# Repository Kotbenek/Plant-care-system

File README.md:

# Moved to Codeberg

This repository was moved to Codeberg:
https://codeberg.org/Kotbenek/Plant-care-system

# Plant care system
PCB of the Plant care system

## Board overview

- ATmega32 AVR microcontroller as the heart of the Plant care system
- Terminal block connector for external pump
- Galvanically isolated terminal block connector for external lamp
- AVR ISP connector for AVR programming
- 5V DC input with battery backup:
  - 18650 battery holder for battery operation
  - TP4056 board for battery charging
  - Additional circuitry enabling simultaneous battery charging and system operation
- Microswitch buttons for system parameters setup
- 4-digit 7-segment display for system parameters
- LEDs indicating the currently displayed parameter on 7-segment display

## Images

## External 3D models used in the PCB render

- [TP4056 module](https://grabcad.com/library/03962a-hw107-lithium-battery-charging-module-1)
- [18650 battery holder](https://grabcad.com/library/18650-single-slot-battery-holder-leaded-1)
- [Terminal block](https://grabcad.com/library/degson-dg301-series-5-0mm-terminal-block-pack-1)

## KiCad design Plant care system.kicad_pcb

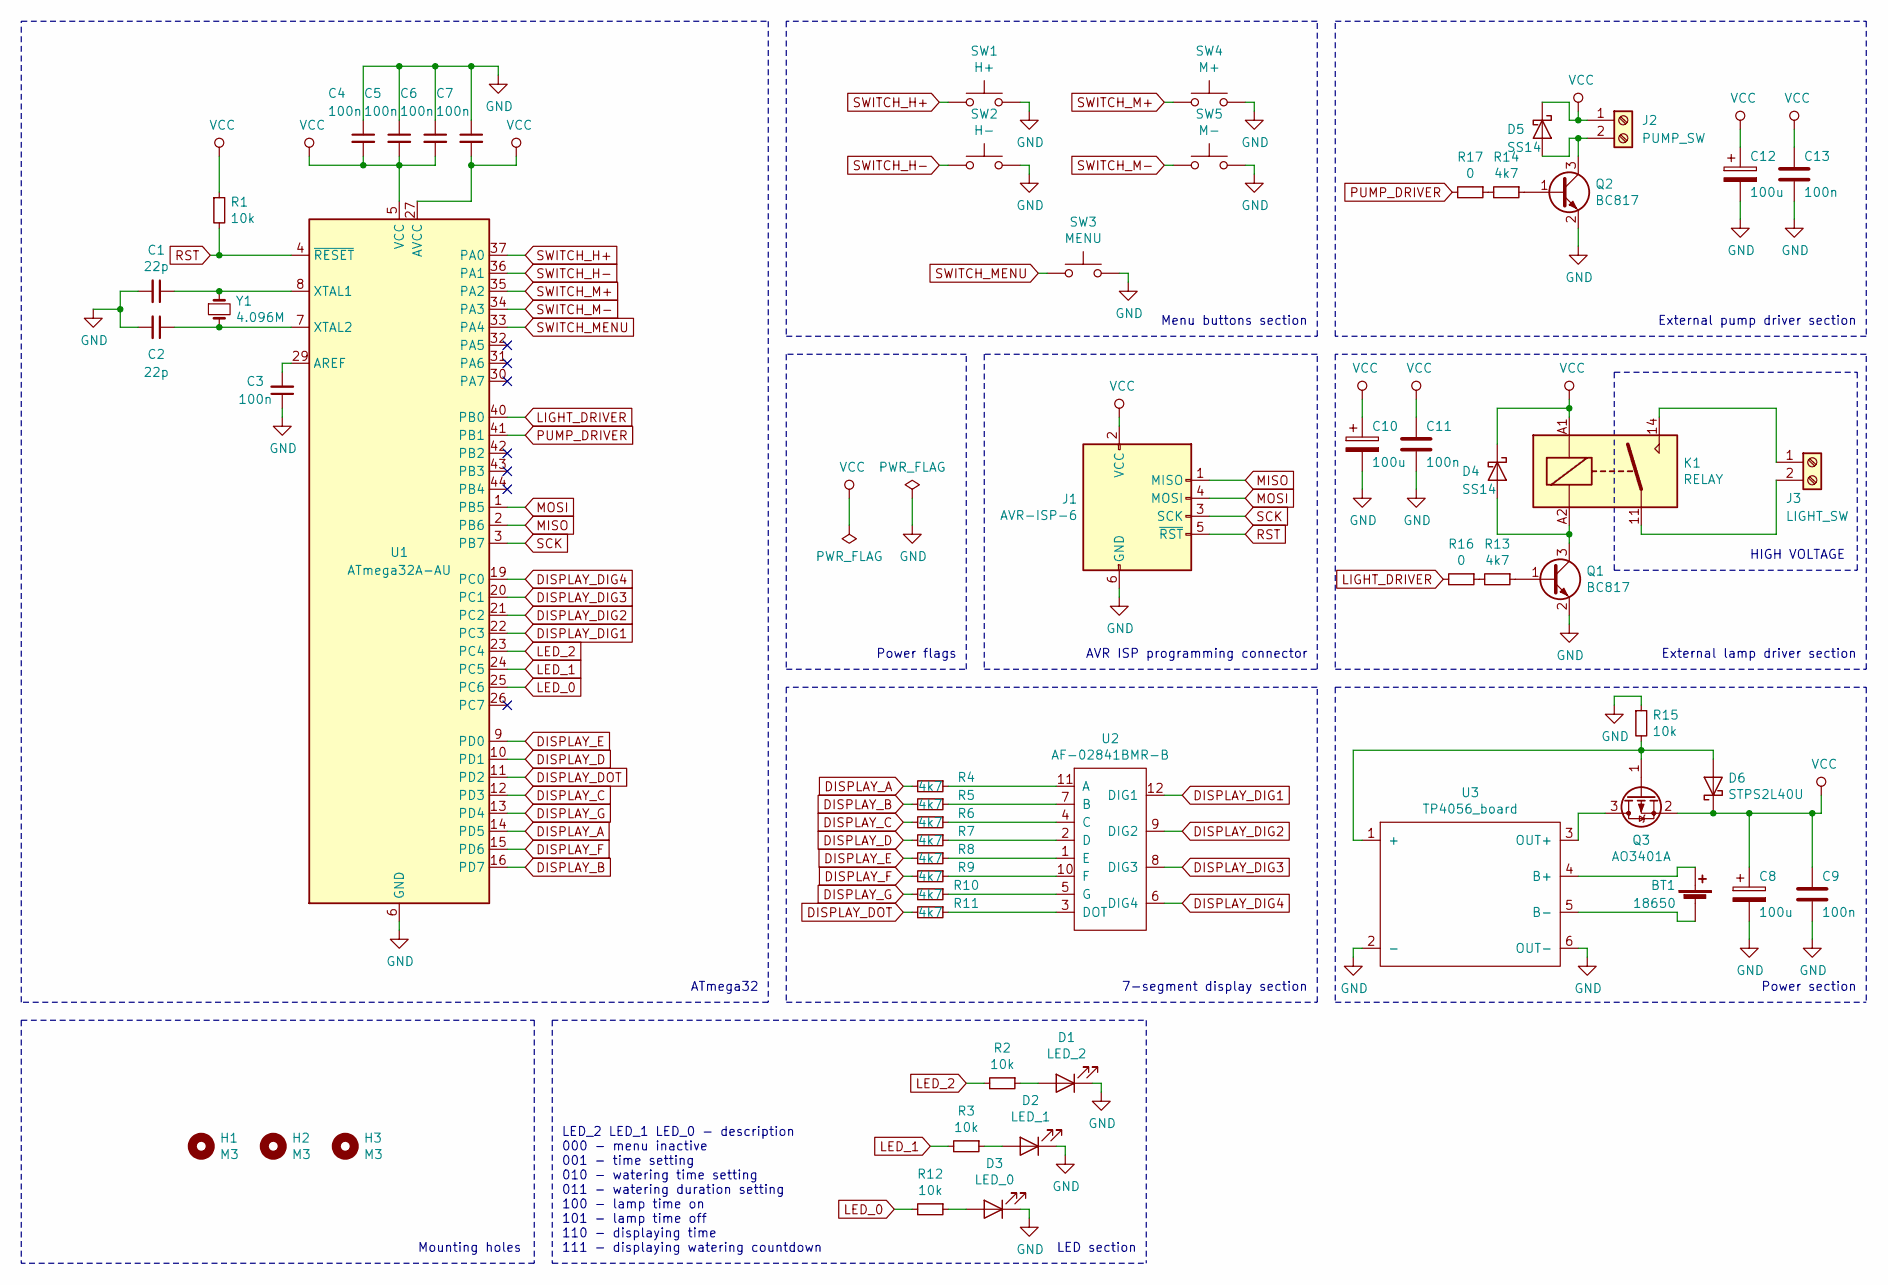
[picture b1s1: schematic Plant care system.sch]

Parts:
BT1: 18650; 18650_holder
C1, C2: 22p; C_0805_2012Metric
C3, C4, C5, C6, C7, C9, C11, C13: 100n; C_0805_2012Metric
C8, C10, C12: 100u; CP_EIA-7343-31_Kemet-D
D1: LED_2; LED_0805_2012Metric
D2: LED_1; LED_0805_2012Metric
D3: LED_0; LED_0805_2012Metric
D4, D5: SS14; D_SMA
D6: STPS2L40U; D_SMB
H1, H2, H3: M3; MountingHole_3.2mm_M3
J1: AVR-ISP-6; PinHeader_2x03_P2.54mm_Vertical
J2: PUMP_SW; DG-301
J3: LIGHT_SW; DG-301
K1: RELAY; Relay_SPDT_Finder_36.11
Q1, Q2: BC817; SOT-23
Q3: AO3401A; SOT-23
R1, R2, R3, R12, R15: 10k; R_0805_2012Metric
R4, R5, R6, R7, R8, R9, R10, R11, R13, R14: 4k7; R_0805_2012Metric
R16, R17: 0; R_1206_3216Metric
SW1: H+; SW_PUSH_6mm_H5mm
SW2: H-; SW_PUSH_6mm_H5mm
SW3: MENU; SW_PUSH_6mm_H5mm
SW4: M+; SW_PUSH_6mm_H5mm
SW5: M-; SW_PUSH_6mm_H5mm
U1: ATmega32A-AU; TQFP-44_10x10mm_P0.8mm
U2: AF-02841BMR-B
U3: TP4056_board
Y1: 4.096M; Crystal_HC49-U_Vertical

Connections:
DISPLAY_A: R4.2, U1.14 (PD5)
DISPLAY_B: R5.2, U1.16 (PD7)
DISPLAY_C: R6.2, U1.12 (PD3)
DISPLAY_D: R7.2, U1.10 (PD1)
DISPLAY_DIG1: U1.22 (PC3), U2.12 (DIG1)
DISPLAY_DIG2: U1.21 (PC2), U2.9 (DIG2)
DISPLAY_DIG3: U1.20 (PC1), U2.8 (DIG3)
DISPLAY_DIG4: U1.19 (PC0), U2.6 (DIG4)
DISPLAY_DOT: R11.2, U1.11 (PD2)
DISPLAY_E: R8.2, U1.9 (PD0)
DISPLAY_F: R9.2, U1.15 (PD6)
DISPLAY_G: R10.2, U1.13 (PD4)
GND: C1.2, C2.2, C3.1, C4.1, C5.1, C6.1, C7.1, C8.2, C9.2, C10.2, C11.2, C12.2, C13.2, D1.1 (K), D2.1 (K), D3.1 (K), J1.6 (GND), Q1.2 (E), Q2.2 (E), R15.1, SW1.2, SW2.2, SW3.2, SW4.2, SW5.2, U1.6 (GND), U1.18 (GND), U1.28 (GND), U1.39 (GND), U3.2 (-), U3.6 (OUT-)
LED_0: R12.2, U1.25 (PC6)
LED_1: R3.2, U1.24 (PC5)
LED_2: R2.2, U1.23 (PC4)
LIGHT_DRIVER: R16.2, U1.40 (PB0)
MISO: J1.1 (MISO), U1.2 (PB6)
MOSI: J1.4 (MOSI), U1.1 (PB5)
unnamed: BT1.1 (+), U3.4 (B+)
unnamed: BT1.2 (-), U3.5 (B-)
unnamed: C1.1, U1.8 (XTAL1), Y1.1
unnamed: C2.1, U1.7 (XTAL2), Y1.2
unnamed: C3.2, U1.29 (AREF)
unnamed: D1.2 (A), R2.1
unnamed: D2.2 (A), R3.1
unnamed: D3.2 (A), R12.1
unnamed: D4.2 (A), K1.A2, Q1.3 (C)
unnamed: D5.2 (A), J2.2, Q2.3 (C)
unnamed: D6.2 (A), Q3.1 (G), R15.2, U3.1 (+)
unnamed: J3.1, K1.14
unnamed: J3.2, K1.11
unnamed: Q1.1 (B), R13.1
unnamed: Q2.1 (B), R14.1
unnamed: Q3.3 (D), U3.3 (OUT+)
unnamed: R4.1, U2.11 (A)
unnamed: R5.1, U2.7 (B)
unnamed: R6.1, U2.4 (C)
unnamed: R7.1, U2.2 (D)
unnamed: R8.1, U2.1 (E)
unnamed: R9.1, U2.10 (F)
unnamed: R10.1, U2.5 (G)
unnamed: R11.1, U2.3 (DOT)
unnamed: R13.2, R16.1
unnamed: R14.2, R17.1
PUMP_DRIVER: R17.2, U1.41 (PB1)
RST: J1.5 (~RST), R1.2, U1.4 (~RESET)
SCK: J1.3 (SCK), U1.3 (PB7)
SWITCH_H+: SW1.1, U1.37 (PA0)
SWITCH_H-: SW2.1, U1.36 (PA1)
SWITCH_M+: SW4.1, U1.35 (PA2)
SWITCH_M-: SW5.1, U1.34 (PA3)
SWITCH_MENU: SW3.1, U1.33 (PA4)
VCC: C4.2, C5.2, C6.2, C7.2, C8.1, C9.1, C10.1, C11.1, C12.1, C13.1, D4.1 (K), D5.1 (K), D6.1 (K), J1.2 (VCC), J2.1, K1.A1, Q3.2 (S), R1.1, U1.5 (VCC), U1.17 (VCC), U1.27 (AVCC), U1.38 (VCC)

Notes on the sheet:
Power section
External lamp driver section
External pump driver section
AVR ISP programming connector
7-segment display section
Power flags
ATmega32
Menu buttons section
LED section
LED_2 LED_1 LED_0 - description 000 - menu inactive 001 - time setting 010 - watering time setting 011 - watering duration setting 100 - lamp time on 101 - lamp time off 110 - displaying time 111 - displaying watering countdown
HIGH VOLTAGE
Mounting holes

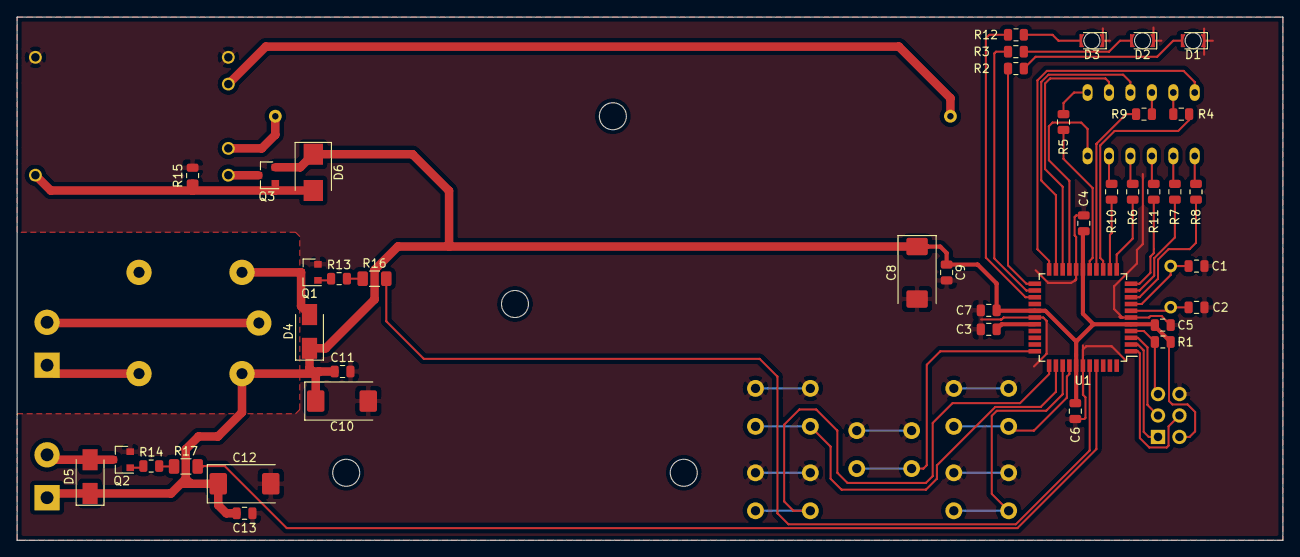
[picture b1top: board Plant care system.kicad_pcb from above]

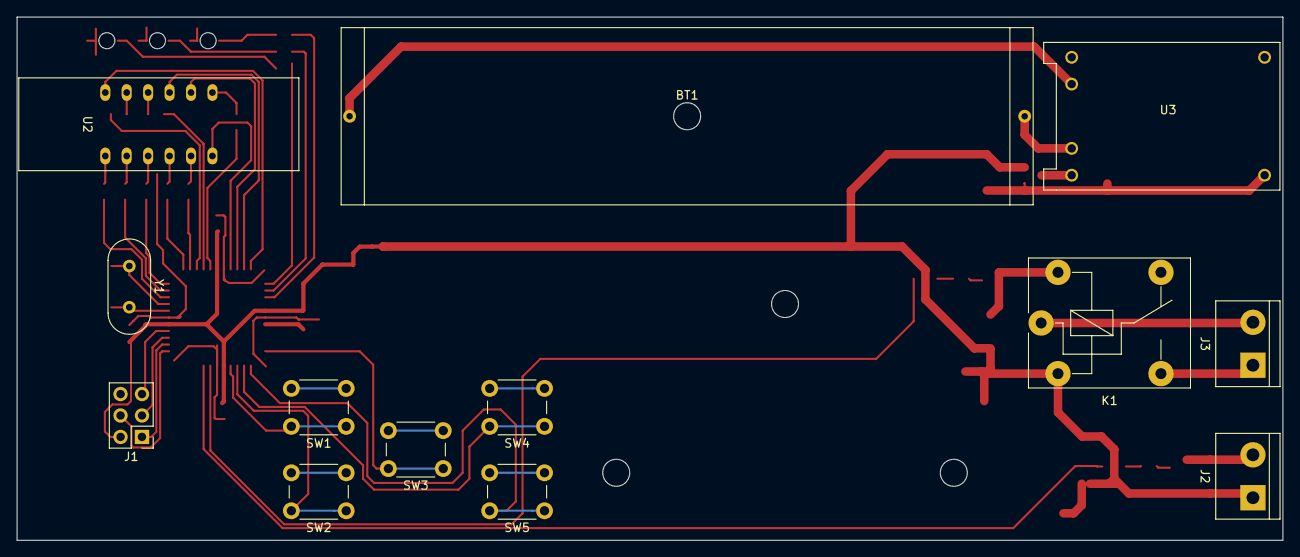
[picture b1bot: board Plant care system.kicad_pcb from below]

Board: 2 copper layers, 150.0 x 62.0 mm, 56 parts (16 on the bottom side), 54 nets.

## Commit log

2021-08-31 Version 1.0
2021-08-31 Added PCB images
2021-08-31 Added gerber files
2021-08-31 Added schematic as pdf file
2021-08-31 Minor PCB update
    - Changed gerber generation settings
2021-09-03 Added missing gerber file
2021-09-03 Added LICENSE.md
2021-09-03 Added README.md
2021-09-24 Added PCB photo
2021-09-24 Changed TP4056 module holes to 1mm
2021-09-24 Updated PCB images
2021-09-28 Updated PCB images
    - Added assembled PCB photos
    - Cropped PCB photo
2021-10-10 Changed LEDs description
2024-09-25 LICENSE.md: Change line breaks from CRLF to LF
2024-09-25 LICENSE.md: Update date
2025-08-17 Moved to Codeberg
